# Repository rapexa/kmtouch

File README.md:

# kmtouch — Mouse & keyboard to touchscreen adapter for Android

**English** | [فارسی](README.fa.md)

kmtouch is a small RP2040-based USB gadget with **two USB-A ports** (mouse + keyboard) and **one USB-C port** (to the phone).
It enumerates on the phone as a standard **HID multitouch touchscreen** and turns key presses and mouse movement into touches at configurable screen positions — like a commercial "keymapper", but open source.
The phone powers everything. **No root, no ADB, no companion app.**

| 3D render | Top copper/silk | Case |
|---|---|---|
|  |  |  |

## How it works
```
mouse ────USB-A─┐
                ├─ FE1.1s hub ── PIO-USB host (GPIO2/3) ─┐
keyboard ─USB-A─┘                                         │  RP2040
phone ◄───USB-C (native USB, device mode) ◄───────────────┘  core1: USB host, core0: touchscreen + mapper
```
- The phone is the USB host and supplies 5 V on VBUS; 5.1 kΩ pull-downs on CC1/CC2 make C-to-C cables work.
- TinyUSB exposes a 5-finger HID touchscreen (0–32767 logical range) plus a regular mouse on the RP2040 native USB port.
- Mouse/keyboard are read through **Pico-PIO-USB** (software USB host on PIO) behind a small FE1.1s hub.
- Android supports HID touchscreens out of the box (`hid-multitouch`).

### Default game mapping
| Input | Action |
|---|---|
| W A S D | Virtual joystick |
| Mouse move | Drag in the camera area (auto re-centres at the edge) |
| Left / right / middle click | Tap fire / aim / … |
| Space, C, R, F, Shift, 1, 2, Tab, Esc | Taps at configured points |
| `` ` `` (grave) | Toggle **game mode** ↔ **pointer mode** (normal Android mouse) |

Up to 5 simultaneous touches (joystick + camera + 3 buttons).

## Repository layout
```
firmware/          C firmware (Pico SDK + TinyUSB + Pico-PIO-USB)
  keymap.json      key mapping — edit this
  tools/           json2keymap.py (generates src/keymap_gen.h at build time)
  src/             main.c, mapper.c, usb_descriptors.c, tusb_config.h
firmware_bin/      prebuilt .uf2 images
hardware/
  kicad/           KiCad 9 project (schematic + routed 60×36 mm 2-layer PCB)
    gen/           Python scripts that generate/place/route the board (run_all.sh)
    tools/         small debug helpers
    out/           fabrication output: Gerber zip, JLCPCB BOM + CPL, renders, schematic PDF
  BOM.csv, netlist.txt, WIRING.md (dev-board wiring)
case/              parametric OpenSCAD case + STLs + previews
```

## Prebuilt firmware
- `firmware_bin/kmtouch_pico_custom_dp2.uf2` — kmtouch PCB, Raspberry Pi Pico or RP2040-Zero (PIO-USB D+ = GPIO2, D− = GPIO3)
- `firmware_bin/kmtouch_feather_usbhost_dp16.uf2` — Adafruit Feather RP2040 USB Host

## Flashing
Hold **BOOTSEL**, plug the board into a computer, copy the `.uf2` onto the `RPI-RP2` drive. It reboots automatically.
On the kmtouch PCB, BOOTSEL and RESET are reachable through pin holes in the lid.

## Building from source
```bash
# needs: cmake, ninja/make, arm-none-eabi-gcc, python3
git clone -b 2.1.1 https://github.com/raspberrypi/pico-sdk && (cd pico-sdk && git submodule update --init lib/tinyusb)
git clone https://github.com/sekigon-gonnoc/Pico-PIO-USB
export PICO_SDK_PATH=$PWD/pico-sdk
cd firmware
cmake -B build -DPICO_PIO_USB_PATH=$PWD/../Pico-PIO-USB
# Feather: cmake -B build -DKMT_PIO_DP_PIN=16 -DPICO_BOARD=adafruit_feather_rp2040_usb_host
cmake --build build        # -> build/kmtouch.uf2
```

## Configuring the keymap
Edit `firmware/keymap.json`. Coordinates are fractions of the **landscape** screen (0.0–1.0, origin top-left).
Use Android *Developer options → Pointer location* to read positions of on-screen game buttons. Rebuild and reflash after editing.

## Hardware
- RP2040, W25Q128JV flash, 12 MHz crystal, AP2112K-3.3 LDO, USB4105 USB-C (UFP), USBLC6-2SC6 ESD, 0.5 A PTC, TPS2051C load switch for USB-A VBUS, FE1.1s hub, 2× Molex 67643 USB-A.
- 60 × 36 mm, 2 layers, 1.6 mm, all SMD parts on top; USB-A connectors are through-hole.
- ERC: 0 violations. DRC (with schematic parity): 0 violations, 0 unconnected.
- Regenerate everything with `hardware/kicad/gen/run_all.sh` (KiCad 9 + Freerouting 1.9).

### Ordering the PCB (JLCPCB)
1. Upload `hardware/kicad/out/kmtouch_gerbers_jlcpcb.zip` (2 layers, 1.6 mm, HASL or ENIG).
2. Enable PCB Assembly (top side) and upload `kmtouch_bom_jlcpcb.csv` and `kmtouch_cpl_jlcpcb.csv`.
3. Check part rotations in the placement preview (QFN/SSOP/SOT-23/USB-C) and part stock; substitute equivalents if needed.
4. USB-A connectors (THT): order THT assembly or hand-solder.

## Case
`case/kmtouch_case.scad` (OpenSCAD, parametric) → `kmtouch_case_base.stl`, `kmtouch_case_lid.stl`. PLA or PETG, 0.2 mm layers, no supports; 4× M2 screws for the PCB and 4× M2 for the lid.

## Limitations
- Firmware compiles but has not been tested on real hardware yet; the PCB has not been fabricated yet — build 5 units first.
- Boot-protocol mouse/keyboard: extra mouse buttons may be ignored.
- USB D+/D− are short traces, not impedance-controlled pairs (fine for Full-Speed 12 Mbps).
- Most phones supply ≈500 mA on OTG; RGB keyboards may brown out. The phone does not charge while connected.
- Some games may detect or forbid input devices; use responsibly.
- VID/PID are from the pid.codes test range.

## Credits
[hid-remapper](https://github.com/jfedor2/hid-remapper), [Pico-PIO-USB](https://github.com/sekigon-gonnoc/Pico-PIO-USB), [TinyUSB](https://github.com/hathach/tinyusb), Raspberry Pi *Hardware design with RP2040*.

## License
- Firmware and scripts: MIT — [`LICENSE`](LICENSE)
- Hardware (KiCad project, case): CERN-OHL-P v2 — [`hardware/LICENSE`](hardware/LICENSE), also applies to `case/`

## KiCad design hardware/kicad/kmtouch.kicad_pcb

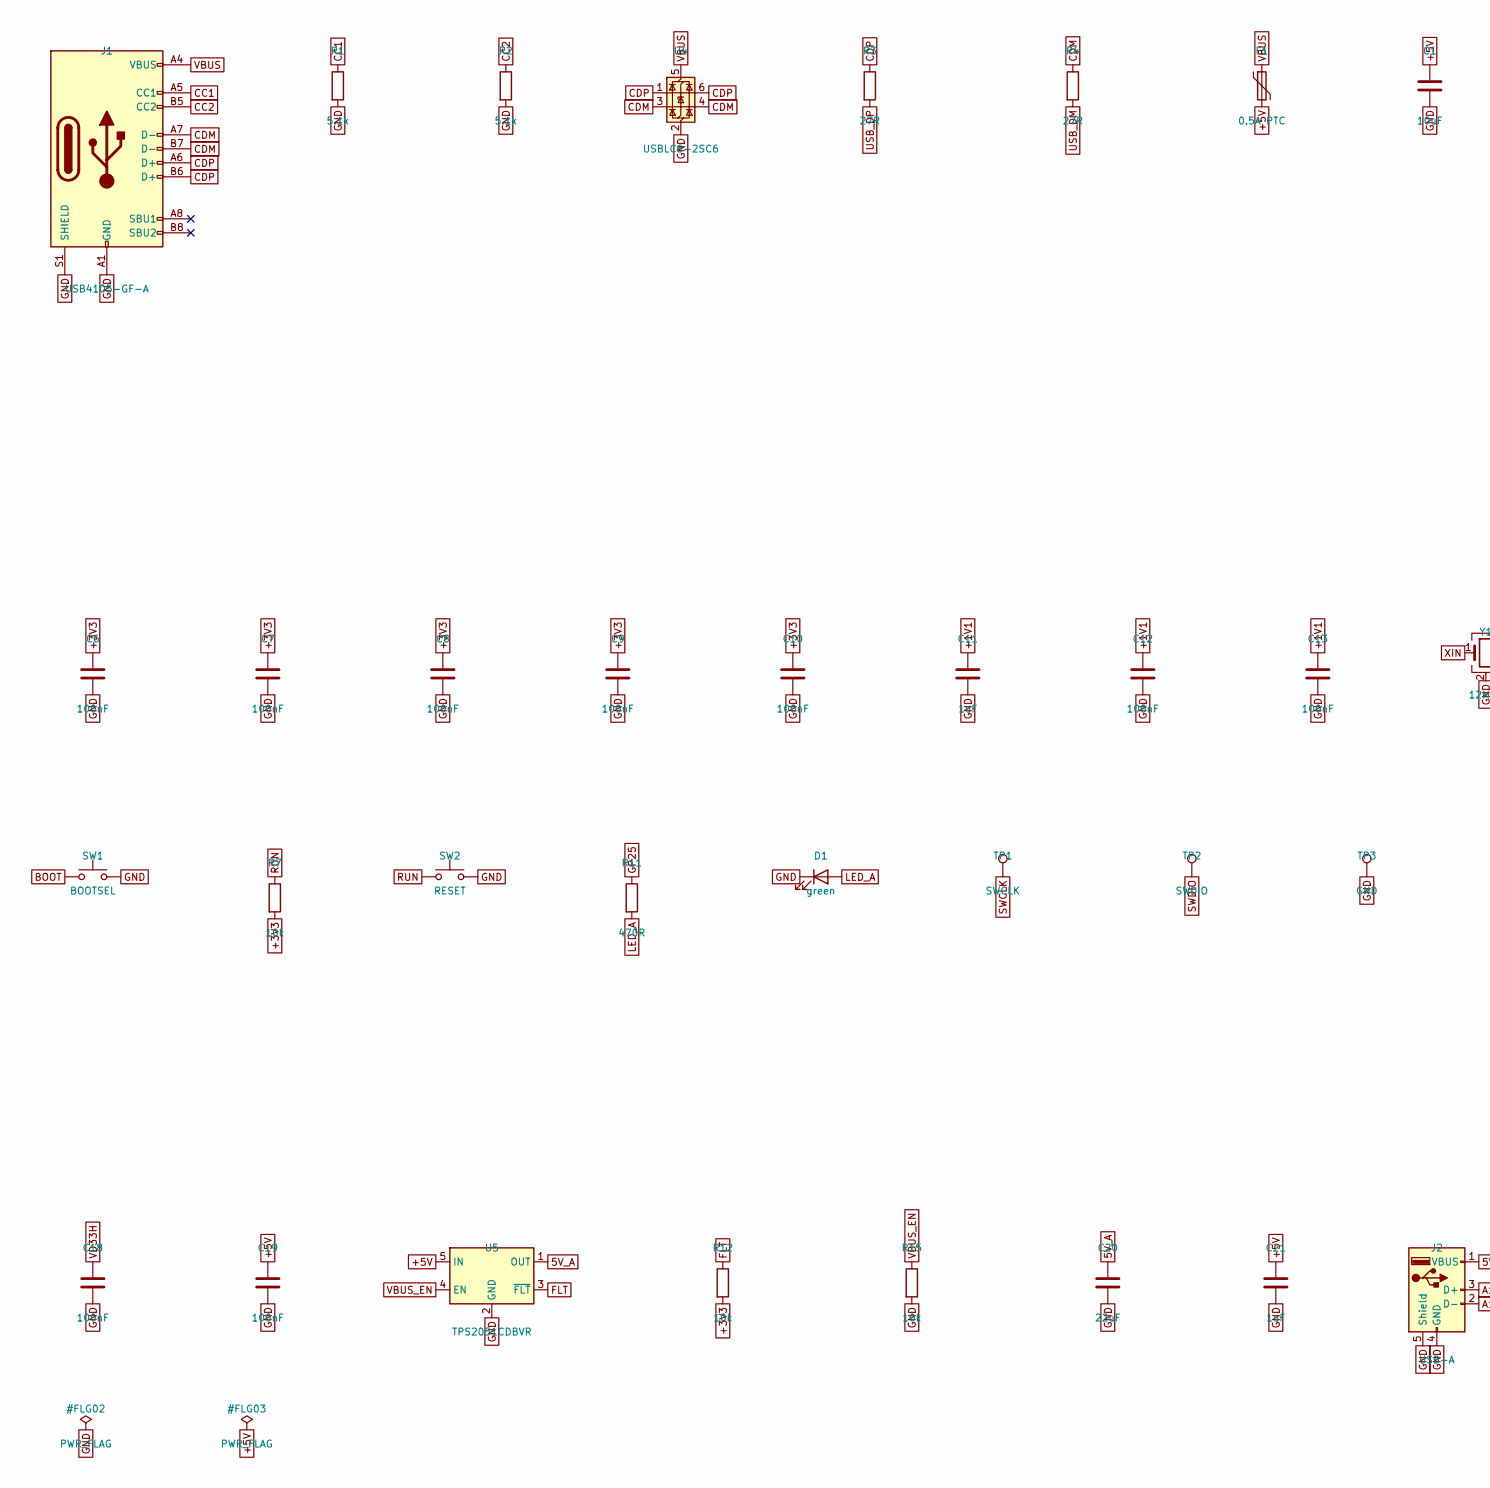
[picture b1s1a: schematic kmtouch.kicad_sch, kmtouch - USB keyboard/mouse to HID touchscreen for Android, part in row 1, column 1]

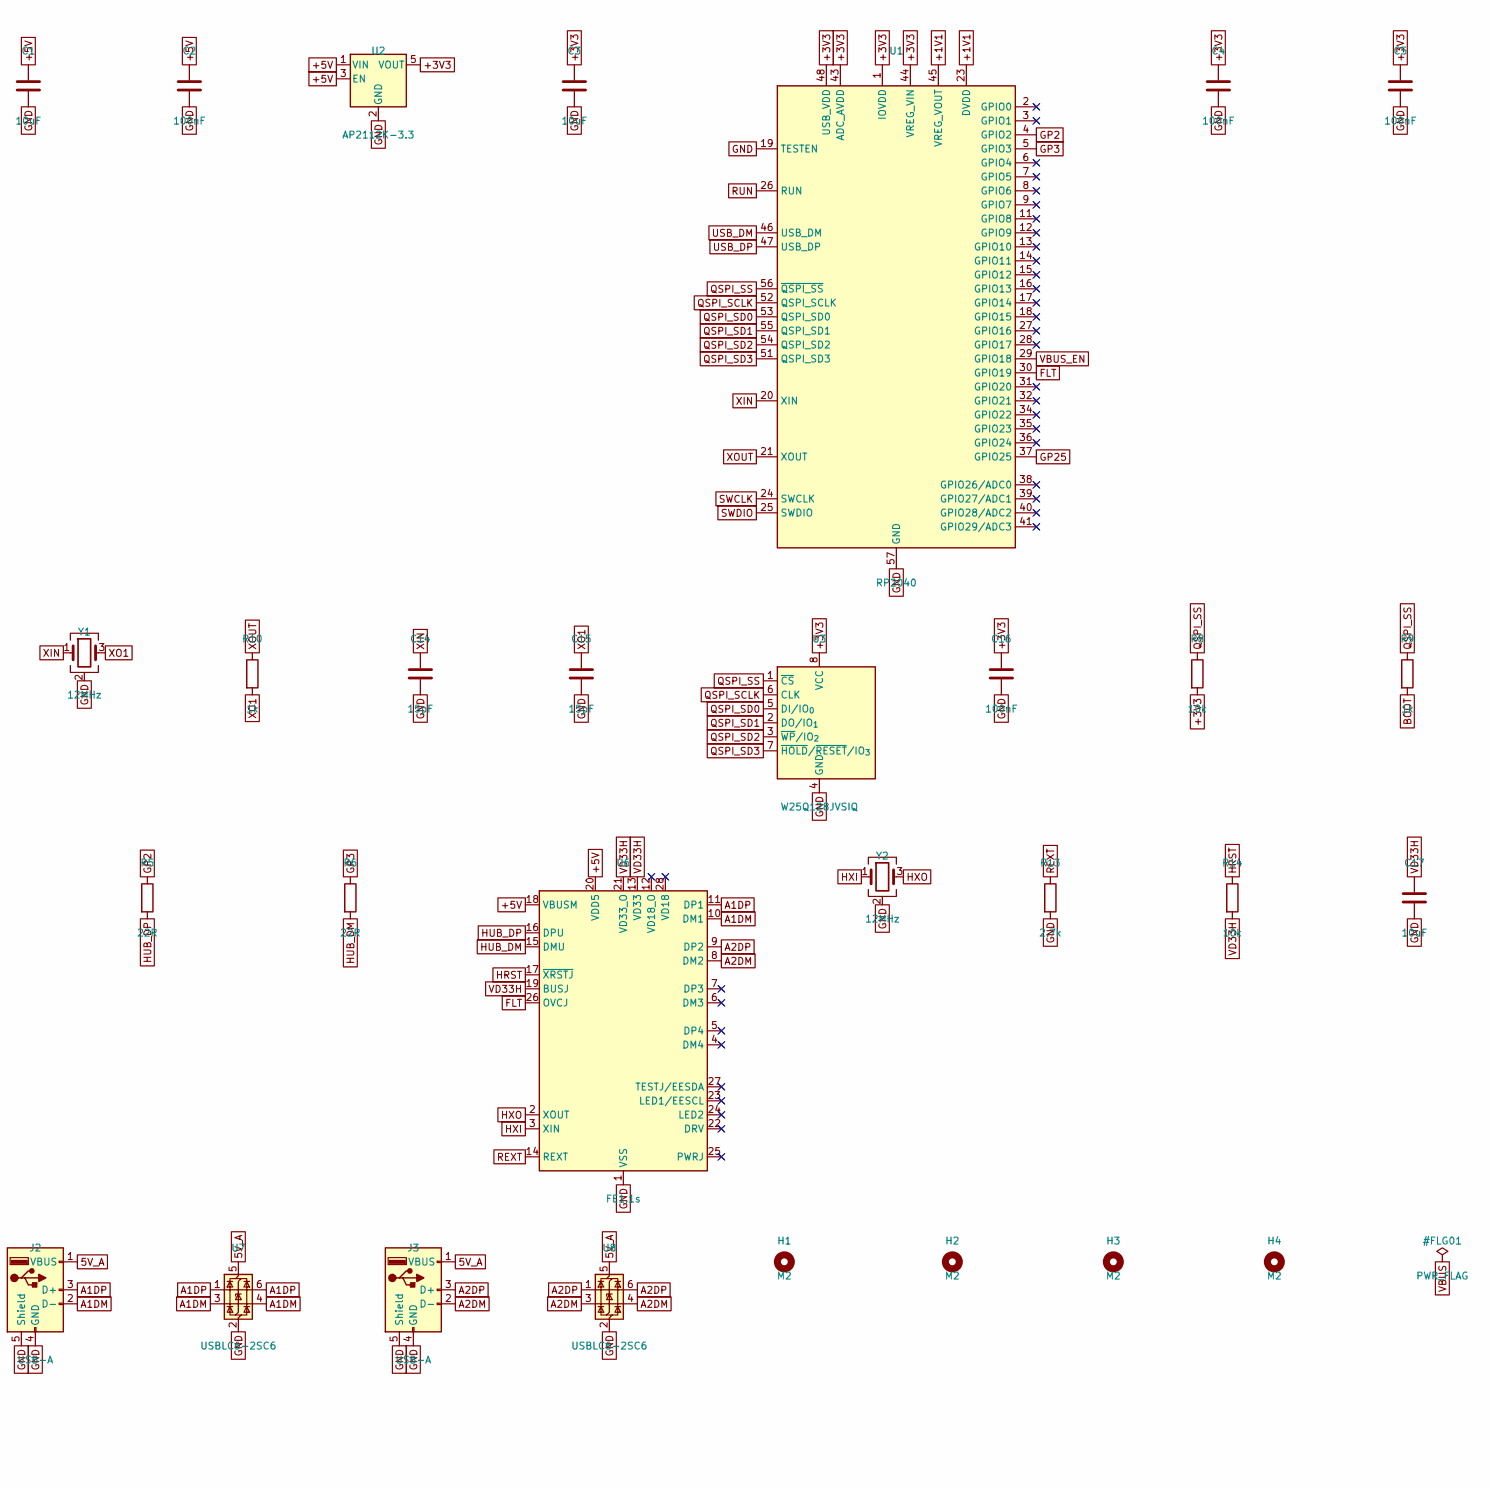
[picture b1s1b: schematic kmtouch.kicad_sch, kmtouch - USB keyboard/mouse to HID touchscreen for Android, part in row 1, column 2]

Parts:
C1, C3, C17: 10uF; C_0805_2012Metric; LCSC C15850
C2, C4, C5, C6, C7, C8, C9, C10, C12, C13, C16, C18, C19: 100nF; C_0402_1005Metric; LCSC C1525
C11, C21: 1uF; C_0402_1005Metric; LCSC C52923
C14, C15: 15pF; C_0402_1005Metric; LCSC C1548
C20: 22uF; C_0805_2012Metric; LCSC C45783
D1: green; LED_0603_1608Metric; LCSC C72043
F1: 0.5A PTC; Fuse_1206_3216Metric; LCSC C70076
H1, H2, H3, H4: M2; MountingHole_2.2mm_M2
J1: USB4105-GF-A; USB_C_Receptacle_GCT_USB4105-xx-A_16P_TopMnt_Horizontal; LCSC C3020560
J2, J3: USB-A; USB_A_Molex_67643_Horizontal; LCSC C19170946
R1, R2: 5.1k; R_0402_1005Metric; LCSC C25905
R3, R4: 27R; R_0402_1005Metric; LCSC C25100
R5, R6: 22R; R_0402_1005Metric; LCSC C25092
R7, R8, R12, R14, R15: 10k; R_0402_1005Metric; LCSC C25744
R9, R10: 1k; R_0402_1005Metric; LCSC C11702
R11: 470R; R_0402_1005Metric; LCSC C25117
R13: 2.7k; R_0402_1005Metric; LCSC C284470
SW1: BOOTSEL; SW_Push_1P1T_XKB_TS-1187A; LCSC C318884
SW2: RESET; SW_Push_1P1T_XKB_TS-1187A; LCSC C318884
TP1: SWCLK; TestPoint_Pad_D1.0mm
TP2: SWDIO; TestPoint_Pad_D1.0mm
TP3: GND; TestPoint_Pad_D1.0mm
U1: RP2040; QFN-56-1EP_7x7mm_P0.4mm_EP3.2x3.2mm; LCSC C2040
U2: AP2112K-3.3; SOT-23-5; LCSC C51118
U3: W25Q128JVSIQ; SOIC-8_5.3x5.3mm_P1.27mm; LCSC C97521
U4, U7, U8: USBLC6-2SC6; SOT-23-6; LCSC C7519
U5: TPS2051CDBVR; SOT-23-5; LCSC C129581
U6: FE1.1s; SSOP-28_3.9x9.9mm_P0.635mm; LCSC C9359
Y1, Y2: 12MHz; Crystal_SMD_3225-4Pin_3.2x2.5mm; LCSC C9002

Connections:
5V_A: C20.1, J2.1 (VBUS), J3.1 (VBUS), U5.1 (OUT), U7.5 (VBUS), U8.5 (VBUS)
+1V1: C11.1, C12.1, C13.1, U1.23 (DVDD), U1.45 (VREG_VOUT), U1.50 (DVDD)
+3V3: C3.1, C4.1, C5.1, C6.1, C7.1, C8.1, C9.1, C10.1, C16.1, R7.2, R8.2, R12.2, U1.1 (IOVDD), U1.10 (IOVDD), U1.22 (IOVDD), U1.33 (IOVDD), U1.42 (IOVDD), U1.43 (ADC_AVDD), U1.44 (VREG_VIN), U1.48 (USB_VDD), U1.49 (IOVDD), U2.5 (VOUT), U3.8 (VCC)
+5V: C1.1, C2.1, C19.1, C21.1, F1.2, U2.1 (VIN), U2.3 (EN), U5.5 (IN), U6.18 (VBUSM), U6.20 (VDD5)
A1DM: J2.2 (D-), U6.10 (DM1), U7.3 (I/O2), U7.4 (I/O2)
A1DP: J2.3 (D+), U6.11 (DP1), U7.1 (I/O1), U7.6 (I/O1)
A2DM: J3.2 (D-), U6.8 (DM2), U8.3 (I/O2), U8.4 (I/O2)
A2DP: J3.3 (D+), U6.9 (DP2), U8.1 (I/O1), U8.6 (I/O1)
BOOT: R9.2, SW1.1
CC1: J1.A5 (CC1), R1.1
CC2: J1.B5 (CC2), R2.1
CDM: J1.A7 (D-), J1.B7 (D-), R4.1, U4.3 (I/O2), U4.4 (I/O2)
CDP: J1.A6 (D+), J1.B6 (D+), R3.1, U4.1 (I/O1), U4.6 (I/O1)
FLT: R12.1, U1.30 (GPIO19), U5.3 (~FLT), U6.26 (OVCJ)
GND: C1.2, C2.2, C3.2, C4.2, C5.2, C6.2, C7.2, C8.2, C9.2, C10.2, C11.2, C12.2, C13.2, C14.2, C15.2, C16.2, C17.2, C18.2, C19.2, C20.2, C21.2, D1.1 (K), J1.A1 (GND), J1.A12 (GND), J1.B1 (GND), J1.B12 (GND), J1.S1 (SHIELD), J2.4 (GND), J2.5 (Shield), J3.4 (GND), J3.5 (Shield), R1.2, R2.2, R13.2, R15.2, SW1.2, SW2.2, TP3.1, U1.19 (TESTEN), U1.57 (GND), U2.2 (GND), U3.4 (GND), U4.2 (GND), U5.2 (GND), U6.1 (VSS), U7.2 (GND), U8.2 (GND), Y1.2 (G), Y1.4 (G), Y2.2 (G), Y2.4 (G)
GP2: R5.1, U1.4 (GPIO2)
GP3: R6.1, U1.5 (GPIO3)
GP25: R11.1, U1.37 (GPIO25)
HRST: R14.1, U6.17 (~XRSTJ)
HUB_DM: R6.2, U6.15 (DMU)
HUB_DP: R5.2, U6.16 (DPU)
HXI: U6.3 (XIN), Y2.1
HXO: U6.2 (XOUT), Y2.3
LED_A: D1.2 (A), R11.2
QSPI_SCLK: U1.52 (QSPI_SCLK), U3.6 (CLK)
QSPI_SD0: U1.53 (QSPI_SD0), U3.5 (DI/IO_{0})
QSPI_SD1: U1.55 (QSPI_SD1), U3.2 (DO/IO_{1})
QSPI_SD2: U1.54 (QSPI_SD2), U3.3 (~WP/IO_{2})
QSPI_SD3: U1.51 (QSPI_SD3), U3.7 (~HOLD/~RESET/IO_{3})
QSPI_SS: R8.1, R9.1, U1.56 (~QSPI_SS), U3.1 (~CS)
REXT: R13.1, U6.14 (REXT)
RUN: R7.1, SW2.1, U1.26 (RUN)
SWCLK: TP1.1, U1.24 (SWCLK)
SWDIO: TP2.1, U1.25 (SWDIO)
USB_DM: R4.2, U1.46 (USB_DM)
USB_DP: R3.2, U1.47 (USB_DP)
VBUS: F1.1, J1.A4 (VBUS), J1.A9 (VBUS), J1.B4 (VBUS), J1.B9 (VBUS), U4.5 (VBUS)
VBUS_EN: R15.1, U1.29 (GPIO18), U5.4 (EN)
VD33H: C17.1, C18.1, R14.2, U6.13 (VD33), U6.19 (BUSJ), U6.21 (VD33_O)
XIN: C14.1, U1.20 (XIN), Y1.1
XO1: C15.1, R10.2, Y1.3
XOUT: R10.1, U1.21 (XOUT)

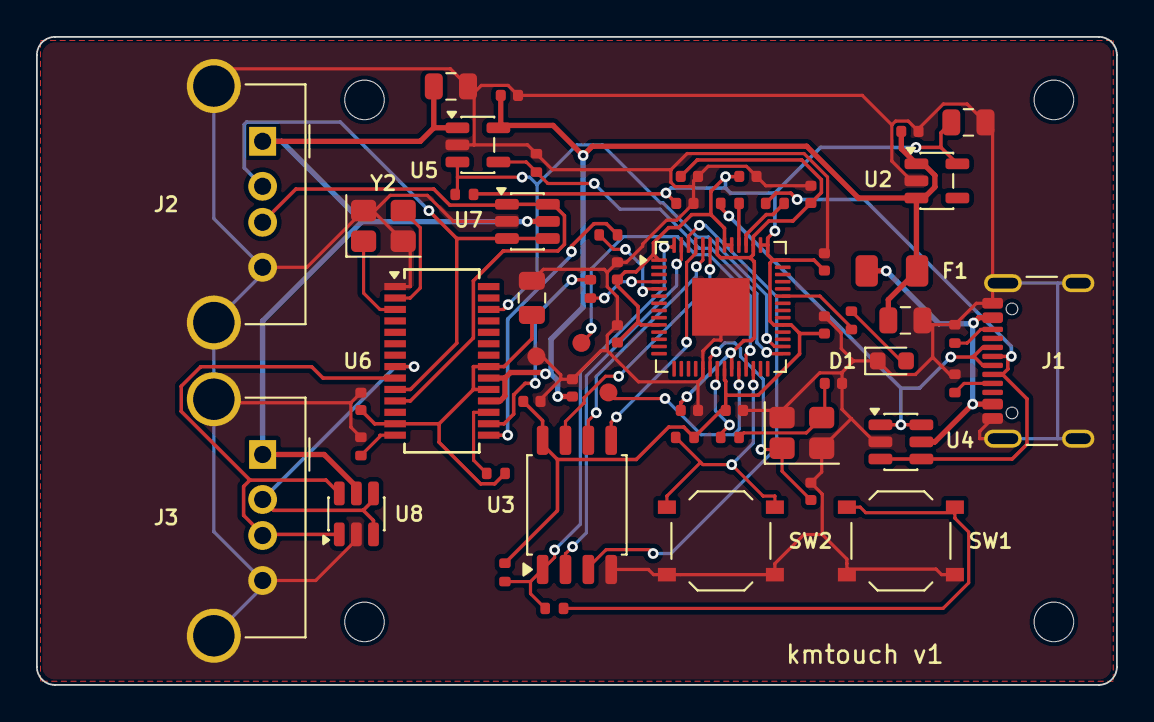
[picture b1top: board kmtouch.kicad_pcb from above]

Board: 2 copper layers, 60.0 x 36.0 mm, 60 parts (0 on the bottom side), 42 nets.

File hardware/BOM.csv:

Ref,Value,Footprint,LCSC
C1,10uF,Capacitor_SMD:C_0805_2012Metric,C15850
C10,100nF,Capacitor_SMD:C_0402_1005Metric,C1525
C11,1uF,Capacitor_SMD:C_0402_1005Metric,C52923
C12,100nF,Capacitor_SMD:C_0402_1005Metric,C1525
C13,100nF,Capacitor_SMD:C_0402_1005Metric,C1525
C14,15pF,Capacitor_SMD:C_0402_1005Metric,C1548
C15,15pF,Capacitor_SMD:C_0402_1005Metric,C1548
C16,100nF,Capacitor_SMD:C_0402_1005Metric,C1525
C17,10uF,Capacitor_SMD:C_0805_2012Metric,C15850
C18,100nF,Capacitor_SMD:C_0402_1005Metric,C1525
C19,100nF,Capacitor_SMD:C_0402_1005Metric,C1525
C2,100nF,Capacitor_SMD:C_0402_1005Metric,C1525
C20,22uF,Capacitor_SMD:C_0805_2012Metric,C45783
C21,1uF,Capacitor_SMD:C_0402_1005Metric,C52923
C3,10uF,Capacitor_SMD:C_0805_2012Metric,C15850
C4,100nF,Capacitor_SMD:C_0402_1005Metric,C1525
C5,100nF,Capacitor_SMD:C_0402_1005Metric,C1525
C6,100nF,Capacitor_SMD:C_0402_1005Metric,C1525
C7,100nF,Capacitor_SMD:C_0402_1005Metric,C1525
C8,100nF,Capacitor_SMD:C_0402_1005Metric,C1525
C9,100nF,Capacitor_SMD:C_0402_1005Metric,C1525
D1,green,LED_SMD:LED_0603_1608Metric,C72043
F1,0.5A PTC,Fuse:Fuse_1206_3216Metric,C70076
H1,M2,MountingHole:MountingHole_2.2mm_M2,
H2,M2,MountingHole:MountingHole_2.2mm_M2,
H3,M2,MountingHole:MountingHole_2.2mm_M2,
H4,M2,MountingHole:MountingHole_2.2mm_M2,
J1,USB4105-GF-A,Connector_USB:USB_C_Receptacle_GCT_USB4105-xx-A_16P_TopMnt_Horizontal,C3020560
J2,USB-A,Connector_USB:USB_A_Molex_67643_Horizontal,C19170946
J3,USB-A,Connector_USB:USB_A_Molex_67643_Horizontal,C19170946
R1,5.1k,Resistor_SMD:R_0402_1005Metric,C25905
R10,1k,Resistor_SMD:R_0402_1005Metric,C11702
R11,470R,Resistor_SMD:R_0402_1005Metric,C25117
R12,10k,Resistor_SMD:R_0402_1005Metric,C25744
R13,2.7k,Resistor_SMD:R_0402_1005Metric,C284470
R14,10k,Resistor_SMD:R_0402_1005Metric,C25744
R15,10k,Resistor_SMD:R_0402_1005Metric,C25744
R2,5.1k,Resistor_SMD:R_0402_1005Metric,C25905
R3,27R,Resistor_SMD:R_0402_1005Metric,C25100
R4,27R,Resistor_SMD:R_0402_1005Metric,C25100
R5,22R,Resistor_SMD:R_0402_1005Metric,C25092
R6,22R,Resistor_SMD:R_0402_1005Metric,C25092
R7,10k,Resistor_SMD:R_0402_1005Metric,C25744
R8,10k,Resistor_SMD:R_0402_1005Metric,C25744
R9,1k,Resistor_SMD:R_0402_1005Metric,C11702
SW1,BOOTSEL,Button_Switch_SMD:SW_Push_1P1T_XKB_TS-1187A,C318884
SW2,RESET,Button_Switch_SMD:SW_Push_1P1T_XKB_TS-1187A,C318884
TP1,SWCLK,TestPoint:TestPoint_Pad_D1.0mm,
TP2,SWDIO,TestPoint:TestPoint_Pad_D1.0mm,
TP3,GND,TestPoint:TestPoint_Pad_D1.0mm,
U1,RP2040,Package_DFN_QFN:QFN-56-1EP_7x7mm_P0.4mm_EP3.2x3.2mm,C2040
U2,AP2112K-3.3,Package_TO_SOT_SMD:SOT-23-5,C51118
U3,W25Q128JVSIQ,Package_SO:SOIC-8_5.3x5.3mm_P1.27mm,C97521
U4,USBLC6-2SC6,Package_TO_SOT_SMD:SOT-23-6,C7519
U5,TPS2051CDBVR,Package_TO_SOT_SMD:SOT-23-5,C129581
U6,FE1.1s,Package_SO:SSOP-28_3.9x9.9mm_P0.635mm,C9359
U7,USBLC6-2SC6,Package_TO_SOT_SMD:SOT-23-6,C7519
U8,USBLC6-2SC6,Package_TO_SOT_SMD:SOT-23-6,C7519
Y1,12MHz,Crystal:Crystal_SMD_3225-4Pin_3.2x2.5mm,C9002
Y2,12MHz,Crystal:Crystal_SMD_3225-4Pin_3.2x2.5mm,C9002

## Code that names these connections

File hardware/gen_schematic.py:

#!/usr/bin/env python3
"""Generates schematic.svg (block-level schematic with pin-level nets)."""
from xml.sax.saxutils import escape
E = lambda t: escape(t.replace('&lt;', '<'))
W,H=1500,980
o=[f'<svg xmlns="http://www.w3.org/2000/svg" width="{W}" height="{H}" font-family="monospace" font-size="13">',
   f'<rect width="{W}" height="{H}" fill="white"/>',
   '<text x="20" y="30" font-size="20" font-weight="bold">kmtouch - USB mouse+keyboard to HID multitouch (RP2040) - schematic v1.0</text>']
def box(x,y,w,h,title,pins_l=(),pins_r=(),color="#eef4ff"):
    o.append(f'<rect x="{x}" y="{y}" width="{w}" height="{h}" fill="{color}" stroke="black" stroke-width="2" rx="6"/>')
    o.append(f'<text x="{x+w/2}" y="{y+20}" text-anchor="middle" font-weight="bold">{E(title)}</text>')
    for i,p in enumerate(pins_l): o.append(f'<text x="{x+6}" y="{y+42+i*18}">{E(p)}</text>')
    for i,p in enumerate(pins_r): o.append(f'<text x="{x+w-6}" y="{y+42+i*18}" text-anchor="end">{E(p)}</text>')
def wire(pts,label=None,color="black"):
    d=" ".join(f"{x},{y}" for x,y in pts)
    o.append(f'<polyline points="{d}" fill="none" stroke="{color}" stroke-width="2"/>')
    if label: x,y=pts[0]; o.append(f'<text x="{x+4}" y="{y-5}" fill="{color}" font-size="12">{E(label)}</text>')
R="#c00000"; G="#006000"; B="#0040c0"
# J1 USB-C
box(30,80,230,230,"J1 USB-C receptacle (UFP)",["VBUS (A4/A9/B4/B9)","CC1 (A5) -R1 5.1k- GND","CC2 (B5) -R2 5.1k- GND","D+ (A6/B6)","D- (A7/B7)","GND","SHIELD -1M||4.7nF- GND"])
box(30,340,230,110,"U4 USBLC6-2SC6 (ESD)",["I/O1 = D+ , I/O2 = D-","VBUS pin = VBUS_IN","GND"],color="#fff4e0")
box(30,480,230,120,"F1 PTC 0.5A (MF-MSMF050-2)",["VBUS_IN -> F1 -> 5V_SYS","C: 10uF + 100nF on 5V_SYS"],color="#fff4e0")
box(30,630,230,150,"U2 AP2112K-3.3 (LDO)",["VIN, EN  &lt;- 5V_SYS","VOUT -> 3V3 (600mA)","CIN 1uF, COUT 1uF","GND"],color="#fff4e0")
# RP2040
box(420,80,420,560,"U1 RP2040 (QFN-56)",
 ["USB_DP (47) -R3 27R- J1.D+","USB_DM (46) -R4 27R- J1.D-","","XIN (20) / XOUT (21)","  Y1 12MHz ABM8-272-T3","  2x 15pF, 1k on XOUT","QSPI_SS/SD0-3/SCLK","  -> U3 W25Q16JVUXIQ","  SS: 10k pull-up, BOOTSEL","","IOVDD/USB_VDD/ADC_VDD &lt;- 3V3","VREG_VIN &lt;- 3V3, VREG_VOUT->DVDD","  (1.1V, 1uF)","DVDD x2 100nF; 3V3 x8 100nF","RUN: 10k pull-up + RESET btn","TESTEN, GND pad -> GND"],
 ["GPIO2 -R5 22R- PIO_DP","GPIO3 -R6 22R- PIO_DM","","GPIO18 -> U5.EN (VBUS_A_EN)","GPIO19 &lt;- U5.FLG (opt.)","GPIO25 -> LED (330R)","","SWDIO/SWCLK -> TP1/TP2","","","BOOTSEL btn:","QSPI_SS-1k-GND"])
# flash
box(420,670,420,110,"U3 W25Q16JVUXIQ 2MB QSPI flash",["/CS=QSPI_SS  CLK=QSPI_SCLK","IO0..IO3 = QSPI_SD0..SD3","VCC=3V3 (100nF)"],color="#eef4ff")
# Hub
box(960,80,300,330,"U6 FE1.1s USB2.0 hub (SSOP-28)",["USBDP0/DM0 &lt;- PIO_DP/DM","  (upstream, full-speed)","XIN/XOUT: Y2 12MHz +","  2x 20pF (per datasheet)","VDD5 &lt;- 5V_A, VD33 1uF","VD18 1uF","RESET: 10k/10uF RC","DP1/DM1 -> J2","DP2/DM2 -> J3","DP3,DP4 unused","PWRJ/OVCJ: tie per DS"],[],color="#eefff0")
# load switch
box(960,440,300,150,"U5 TPS2051C / AP2553 (load sw)",["IN &lt;- 5V_SYS","EN &lt;- GPIO18","OUT -> 5V_A (500mA lim.)","FLG -> GPIO19 (10k PU)","COUT 47uF on 5V_A"],[],color="#fff4e0")
# USB-A
box(1300,80,180,150,"J2 USB-A (mouse)",["1 VBUS &lt;- 5V_A","2 D- &lt;- U6.DM1","3 D+ &lt;- U6.DP1","4 GND"],color="#f4eeff")
box(1300,260,180,150,"J3 USB-A (keyb.)",["1 VBUS &lt;- 5V_A","2 D- &lt;- U6.DM2","3 D+ &lt;- U6.DP2","4 GND"],color="#f4eeff")
box(1300,440,180,150,"U7,U8 USBLC6",["one per USB-A","on D+/D-","and 5V_A"],color="#fff4e0")
# wires
wire([(260,190),(420,190)],"D+/D- (via R3/R4 27R)",B)
wire([(260,520),(330,520),(330,600)],"5V_SYS",R)
wire([(260,140),(300,140),(300,520)],"VBUS_IN",R)
wire([(260,700),(420,700)],"3V3",R)
wire([(840,120),(960,120)],"PIO_DP/PIO_DM",B)
wire([(840,390),(900,390),(900,480),(960,480)],"VBUS_A_EN",G)
wire([(1260,520),(1280,520),(1280,120),(1300,120)],"5V_A",R)
wire([(1260,250),(1300,250)],"DP1/DM1, DP2/DM2",B)
o.append('<text x="20" y="830" font-size="14">Notes: Phone is USB host and powers everything via J1 VBUS (5V). CC1/CC2 5.1k to GND = UFP (sink), so phone turns on VBUS.</text>')
o.append('<text x="20" y="852" font-size="14">PIO-USB host runs on GPIO2/3 (D-=D+ +1, required). One PIO-USB root port -> FE1.1s hub -> 2x USB-A, so TinyUSB can enumerate both devices.</text>')
o.append('<text x="20" y="874" font-size="14">Alt (no hub): 2nd PIO-USB root port on GPIO4/5 via pio_usb_host_add_port() - needs custom host code (not TinyUSB), see README.</text>')
o.append('<text x="20" y="896" font-size="14">Budget: RP2040+hub ~50mA, mouse+kbd ~100-200mA. Many phones limit OTG to 500mA. LED/RGB keyboards may exceed it.</text>')
o.append('<text x="20" y="918" font-size="14">Reference: RP2040 "Hardware design with RP2040" minimal design; Adafruit Feather RP2040 USB Host; jfedor2/hid-remapper.</text>')
o.append('</svg>')
open("schematic.svg","w").write("\n".join(o))

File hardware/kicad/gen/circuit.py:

# Single source of truth for kmtouch circuit: parts, footprints, LCSC, nets.
R0402="Resistor_SMD:R_0402_1005Metric"; C0402="Capacitor_SMD:C_0402_1005Metric"
C0603="Capacitor_SMD:C_0603_1608Metric"; C0805="Capacitor_SMD:C_0805_2012Metric"
LCSC_R={"5.1k":"C25905","27R":"C25100","22R":"C25092","1k":"C11702","10k":"C25744","2.7k":"C284470","470R":"C25117"}
LCSC_C={"100nF":"C1525","1uF":"C52923","15pF":"C1548","10uF":"C15850","22uF":"C45783"}
P=[]
def part(ref,sym,fp,val,lcsc,pins,anchor=None,place=None):
    P.append(dict(ref=ref,sym=sym,fp=fp,val=val,lcsc=lcsc,pins=pins,anchor=anchor,place=place))
def R(ref,val,a,b,anchor=None): part(ref,"Device:R",R0402,val,LCSC_R[val],{"1":a,"2":b},anchor)
def C(ref,val,a,b="GND",anchor=None):
    fp=C0805 if val in("10uF","22uF") else C0402
    part(ref,"Device:C",fp,val,LCSC_C[val],{"1":a,"2":b},anchor)

# --- USB-C upstream (to phone) ---
part("J1","Connector:USB_C_Receptacle_USB2.0_16P","Connector_USB:USB_C_Receptacle_GCT_USB4105-xx-A_16P_TopMnt_Horizontal","USB4105-GF-A","C3020560",
 {"A1":"GND","A12":"GND","B1":"GND","B12":"GND","A4":"VBUS","A9":"VBUS","B4":"VBUS","B9":"VBUS",
  "A5":"CC1","B5":"CC2","A6":"CDP","B6":"CDP","A7":"CDM","B7":"CDM","S1":"GND"})
R("R1","5.1k","CC1","GND",("J1","A5")); R("R2","5.1k","CC2","GND",("J1","B5"))
part("U4","Power_Protection:USBLC6-2SC6","Package_TO_SOT_SMD:SOT-23-6","USBLC6-2SC6","C7519",
 {"1":"CDP","6":"CDP","3":"CDM","4":"CDM","2":"GND","5":"VBUS"})
R("R3","27R","CDP","USB_DP",("U1","47")); R("R4","27R","CDM","USB_DM",("U1","46"))
part("F1","Device:Polyfuse","Fuse:Fuse_1206_3216Metric","0.5A PTC","C70076",{"1":"VBUS","2":"+5V"})
C("C1","10uF","+5V",anchor=("F1","2")); C("C2","100nF","+5V",anchor=("U2","1"))
# --- 3.3 V LDO ---
part("U2","Regulator_Linear:AP2112K-3.3","Package_TO_SOT_SMD:SOT-23-5","AP2112K-3.3","C51118",{"1":"+5V","3":"+5V","2":"GND","5":"+3V3"})
C("C3","10uF","+3V3",anchor=("U2","5"))
# --- RP2040 ---
U1={"1":"+3V3","10":"+3V3","22":"+3V3","33":"+3V3","42":"+3V3","49":"+3V3","43":"+3V3","48":"+3V3","44":"+3V3",
    "45":"+1V1","23":"+1V1","50":"+1V1","57":"GND","19":"GND","20":"XIN","21":"XOUT",
    "24":"SWCLK","25":"SWDIO","26":"RUN","46":"USB_DM","47":"USB_DP",
    "56":"QSPI_SS","51":"QSPI_SD3","52":"QSPI_SCLK","53":"QSPI_SD0","54":"QSPI_SD2","55":"QSPI_SD1",
    "4":"GP2","5":"GP3","29":"VBUS_EN","30":"FLT","37":"GP25"}
part("U1","MCU_RaspberryPi:RP2040","Package_DFN_QFN:QFN-56-1EP_7x7mm_P0.4mm_EP3.2x3.2mm","RP2040","C2040",U1)
for i,pin in enumerate(["1","10","22","33","42","49"]): C(f"C{4+i}","100nF","+3V3",anchor=("U1",pin))
C("C10","100nF","+3V3",anchor=("U1","44")); C("C11","1uF","+1V1",anchor=("U1","45"))
C("C12","100nF","+1V1",anchor=("U1","23")); C("C13","100nF","+1V1",anchor=("U1","50"))
part("Y1","Device:Crystal_GND24","Crystal:Crystal_SMD_3225-4Pin_3.2x2.5mm","12MHz","C9002",{"1":"XIN","3":"XO1","2":"GND","4":"GND"},("U1","20"))
R("R10","1k","XOUT","XO1",("U1","21"))
C("C14","15pF","XIN",anchor=("Y1","1")); C("C15","15pF","XO1",anchor=("Y1","3"))
part("U3","Memory_Flash:W25Q128JVS","Package_SO:SOIC-8_5.3x5.3mm_P1.27mm","W25Q128JVSIQ","C97521",
 {"1":"QSPI_SS","2":"QSPI_SD1","3":"QSPI_SD2","4":"GND","5":"QSPI_SD0","6":"QSPI_SCLK","7":"QSPI_SD3","8":"+3V3"})
C("C16","100nF","+3V3",anchor=("U3","8"))
R("R8","10k","QSPI_SS","+3V3",("U3","1")); R("R9","1k","QSPI_SS","BOOT",("U3","1"))
part("SW1","Switch:SW_Push","Button_Switch_SMD:SW_Push_1P1T_XKB_TS-1187A","BOOTSEL","C318884",{"1":"BOOT","2":"GND"},place=(148,128,0))
R("R7","10k","RUN","+3V3",("U1","26"))
part("SW2","Switch:SW_Push","Button_Switch_SMD:SW_Push_1P1T_XKB_TS-1187A","RESET","C318884",{"1":"RUN","2":"GND"},place=(138,128,0))
R("R11","470R","GP25","LED_A",("U1","37"))
part("D1","Device:LED","LED_SMD:LED_0603_1608Metric","green","C72043",{"1":"GND","2":"LED_A"},("R11","2"))
part("TP1","Connector:TestPoint","TestPoint:TestPoint_Pad_D1.0mm","SWCLK","",{"1":"SWCLK"},("U1","24"))
part("TP2","Connector:TestPoint","TestPoint:TestPoint_Pad_D1.0mm","SWDIO","",{"1":"SWDIO"},("U1","25"))
part("TP3","Connector:TestPoint","TestPoint:TestPoint_Pad_D1.0mm","GND","",{"1":"GND"},("TP2","1"))
# --- PIO-USB host -> FE1.1s hub ---
R("R5","22R","GP2","HUB_DP",("U1","4")); R("R6","22R","GP3","HUB_DM",("U1","5"))
part("U6","Interface_USB:FE1.1s","Package_SO:SSOP-28_3.9x9.9mm_P0.635mm","FE1.1s","C9359",
 {"1":"GND","2":"HXO","3":"HXI","10":"A1DM","11":"A1DP","8":"A2DM","9":"A2DP","14":"REXT","15":"HUB_DM","16":"HUB_DP",
  "17":"HRST","18":"+5V","19":"VD33H","20":"+5V","21":"VD33H","13":"VD33H","26":"FLT"},place=(122.5,118,0))
part("Y2","Device:Crystal_GND24","Crystal:Crystal_SMD_3225-4Pin_3.2x2.5mm","12MHz","C9002",{"1":"HXI","3":"HXO","2":"GND","4":"GND"},("U6","2"))
R("R13","2.7k","REXT","GND",("U6","14")); R("R14","10k","HRST","VD33H",("U6","17"))
C("C17","10uF","VD33H",anchor=("U6","21")); C("C18","100nF","VD33H",anchor=("U6","13"))
C("C19","100nF","+5V",anchor=("U6","20"))
# --- downstream VBUS switch ---
part("U5","Power_Management:TPS2051CDBV","Package_TO_SOT_SMD:SOT-23-5","TPS2051CDBVR","C129581",{"1":"5V_A","2":"GND","3":"FLT","4":"VBUS_EN","5":"+5V"},place=(124.5,106,0))
R("R12","10k","FLT","+3V3",("U5","3")); R("R15","10k","VBUS_EN","GND",("U5","4"))
C("C20","22uF","5V_A",anchor=("U5","1")); C("C21","1uF","+5V",anchor=("U5","5"))
for j,(dm,dp,u,y) in {"J2":("A1DM","A1DP","U7",109.3),"J3":("A2DM","A2DP","U8",126.7)}.items():
    part(j,"Connector:USB_A","Connector_USB:USB_A_Molex_67643_Horizontal","USB-A","C19170946",{"1":"5V_A","2":dm,"3":dp,"4":"GND","5":"GND"},place=(100,y,"W"))
    part(u,"Power_Protection:USBLC6-2SC6","Package_TO_SOT_SMD:SOT-23-6","USBLC6-2SC6","C7519",{"1":dp,"6":dp,"3":dm,"4":dm,"2":"GND","5":"5V_A"},(j,"3"))
part("H1","Mechanical:MountingHole","MountingHole:MountingHole_2.2mm_M2","M2","",{},place=(118.2,103.5,0))
part("H2","Mechanical:MountingHole","MountingHole:MountingHole_2.2mm_M2","M2","",{},place=(156.5,103.5,0))
part("H3","Mechanical:MountingHole","MountingHole:MountingHole_2.2mm_M2","M2","",{},place=(118.2,132.5,0))
part("H4","Mechanical:MountingHole","MountingHole:MountingHole_2.2mm_M2","M2","",{},place=(156.5,132.5,0))
# fixed positions for main parts
FIXED={"J1":(160,118,"E"),"U1":(138,115,0),"U3":(130,126,90),"U2":(150,108,0),"F1":(147.5,113,0),"U4":(148,122.5,0)}
for p in P:
    if p["ref"] in FIXED: p["place"]=FIXED[p["ref"]]
NETS=sorted({n for p in P for n in p["pins"].values()})
